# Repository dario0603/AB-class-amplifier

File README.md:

# Class-AB Audio Power Amplifier

## Overview

Design and simulation of a **Class-AB audio power amplifier**, focusing on output-stage linearity, crossover distortion reduction, and overcurrent protection.

The circuit combines an input amplification stage, diode-based biasing, and a complementary power output stage to achieve linear signal amplification. LTspice simulations are used to investigate the amplifier's transient response, frequency behavior, and current-limiting operation.

The project also explores the interaction between output-stage biasing, load current, and protection circuitry.

## Design Calculations

### 1. Power-Supply Smoothing Capacitor

The required smoothing capacitance is estimated using the empirical relationship for a full-wave rectifier:

$$
C \simeq \frac{I_{\mathrm{load}}}{2f \cdot \Delta V}
$$

where:
- $I_{\mathrm{load}}$ is the maximum load current.
- $f$ is the AC supply frequency.
- $\Delta V$ is the maximum allowable peak-to-peak ripple voltage.

Assuming a maximum load current of 3A, limited by the BJT-based output protection circuit, and a maximum ripple voltage of 2V, the required capacitance is approximately 15mF, assuming a 50Hz AC supply.

The implemented solution uses five 4700 $\mu$F capacitors connected in parallel, providing a nominal total capacitance of:

$$
C_{\mathrm{total}} = 5 \times 4700\mu\mathrm{F}
= 23.5\mathrm{mF}
$$

This capacitance exceeds the theoretical minimum and provides additional margin for smoothing the rectified voltage under load.

### 2. Output Current-Limit Protection

The positive and negative output-current limits are set by the current-sensing resistors $R_6$ and $R_7$. Using the approximate base-emitter voltage of a BJT, $V_{BE}\simeq 0.6\mathrm{V}$, the limiting currents can be estimated as:

$$
I_{\mathrm{max}+} \simeq \frac{0.6\mathrm{V}}{R_6}
$$

$$
I_{\mathrm{max}-} \simeq -\frac{0.6\mathrm{V}}{R_7}
$$

For a nominal current limit of approximately $\pm 3\mathrm{A}$, the required resistance values are:

$$
R_6 \simeq R_7 \simeq
\frac{0.6\mathrm{V}}{3\mathrm{A}}
= 0.2\Omega
$$

Using equal sensing resistances provides approximately symmetrical positive and negative current limits. The actual thresholds may differ due to transistor characteristics, temperature, and resistor tolerances.

### 3. Volume Control

Resistors $R_8$ and $R_9$ represent the upper and lower portions of a $10\mathrm{k}\Omega$ potentiometer used to adjust the amplifier's input level.

Rotating the potentiometer changes the voltage delivered to the following amplification stage, thereby controlling the audio volume.

### 4. Output power

Provided that overcurrent limiting is not triggered (i.e., the current remains below 3 A in magnitude), the maximum output voltage is given by \(V_{\mathrm{CC}} - 2V_{\gamma} - V_{\mathrm{ripple}}\). With a 32 V supply, this is approximately

$$
V_{\mathrm{out,max}} \simeq 32\mathrm{V} - 1.2\mathrm{V} - 2\mathrm{V} \simeq 28.8\mathrm{V}
$$

Considering the output voltage swing limitations of the TL082 operational amplifiers, whose maximum output voltage is approximately $V_{\mathrm{CC}} - 1.5\mathrm{V}$ and whose minimum output voltage is approximately \(1.5\mathrm{V}\), the maximum voltage swing is

$$
V_{\mathrm{pp}} \simeq 28.8\mathrm{V} - 1.5\mathrm{V} - 1.5\mathrm{V} \simeq 25.8\mathrm{V}
$$

Assuming a sinusoidal output signal, the maximum output power can be estimated as

$$
P_{\mathrm{out}} = \frac{V_{\mathrm{pp}}^2}{8R_{\mathrm{load}}}
$$

For a $4\Omega$ load, the maximum output power is approximately

$$
P_{\mathrm{out}} = \frac{25.8^2}{8 \cdot 4} \approx 20.8\,\mathrm{W}
$$

For an $8\Omega$ load, the maximum output power is approximately

$$
P_{\mathrm{out}} = \frac{25.8^2}{8 \cdot 8} \approx 10.4\mathrm{W}
$$

To increase the output power, the supply voltage $V\_{\mathrm{CC}}$ must be increased, while ensuring that the maximum supply voltage rating of the TL082 operational amplifiers is not exceeded.

## Simulation Results

### 1. Transient Response

The transient simulation compares the input signal $V_{in}$ with the output signal $V_{out}$.

The output waveform demonstrates the amplifier's ability to reproduce the input sinusoid with increased amplitude. The region around the zero crossing is particularly relevant for evaluating crossover distortion in the Class-AB output stage.

### 2. Frequency Response

The Bode plot shows the output-to-input transfer function in terms of gain magnitude and phase.

The simulated response exhibits a relatively flat passband up to approximately **100 kHz**, followed by high-frequency attenuation. The magnitude and phase responses provide insight into the amplifier's bandwidth and frequency-dependent behavior.

The voltage gain is set to the maximum value for this configuration, $A_v = 11 \simeq 20.8\text{dB}$.

### 3. Output Current Limiting

The current-limit simulation evaluates the behavior of the protection circuit under excessive output-current demand.

The circuit is designed to constrain the load current to approximately **±3 A**, helping protect the output transistors against overload conditions.

### 4. Current-Limit Transient Response

A closer view of the transient response highlights the behavior of the protection circuit during a current-limit event.

The simulation shows the current transient settling toward the intended limiting level. The observed settling time is approximately **12 ms** under the simulated conditions.

## PCB Design

The PCB layout was developed in KiCad based on the Class-AB audio power amplifier schematic. Particular attention was paid to component placement, power-stage routing, and current-carrying traces to ensure reliable operation.

The PCB design aims to minimize unwanted parasitic effects and provide suitable routing for the relatively high currents handled by the output stage. The placement of the output transistors and current-sensing resistors is particularly important for thermal management and current-limit protection.

### 1. PCB Layout

The following image shows the PCB layout designed in KiCad, including component placement and routing.

### 2. 3D PCB View

The 3D visualization provides a preview of the assembled PCB, showing the component placement and overall board layout. This view is useful for inspecting component positioning and evaluating the physical arrangement before manufacturing.

## Repository Structure

```text
.
├── README.md                               # Project documentation
├── img/                                    # Images and simulation results
├── KiCad/                                  # Schematics and PCB designs
│   └── mono_amplifier/
│       ├── AB_amp/                         # Class-AB amplifier design
│       ├── audio equalizer/                # Audio equalizer design
│       ├── mono_amplifier/                 # Main KiCad project — open this project only;
│       │                                   # the other designs are internally linked
│       └── power supply/                   # Power supply design
└── Spice/                                  # LTspice simulations
    └── opamp version/
        ├── AB amplifier final version.asc  # Final amplifier simulation
        ├── AB amplifier v1.asc             # Amplifier simulation, version 1
        ├── AB amplifier v2.asc             # Amplifier simulation, version 2
        └── AB amplifier v3.asc             # Amplifier simulation, version 3
```

> **Important:** Open only the main KiCad project file: `KiCad/mono_amplifier/mono_amplifier/mono_amplifier.kicad_pro`. The other KiCad designs are internally linked to this project.

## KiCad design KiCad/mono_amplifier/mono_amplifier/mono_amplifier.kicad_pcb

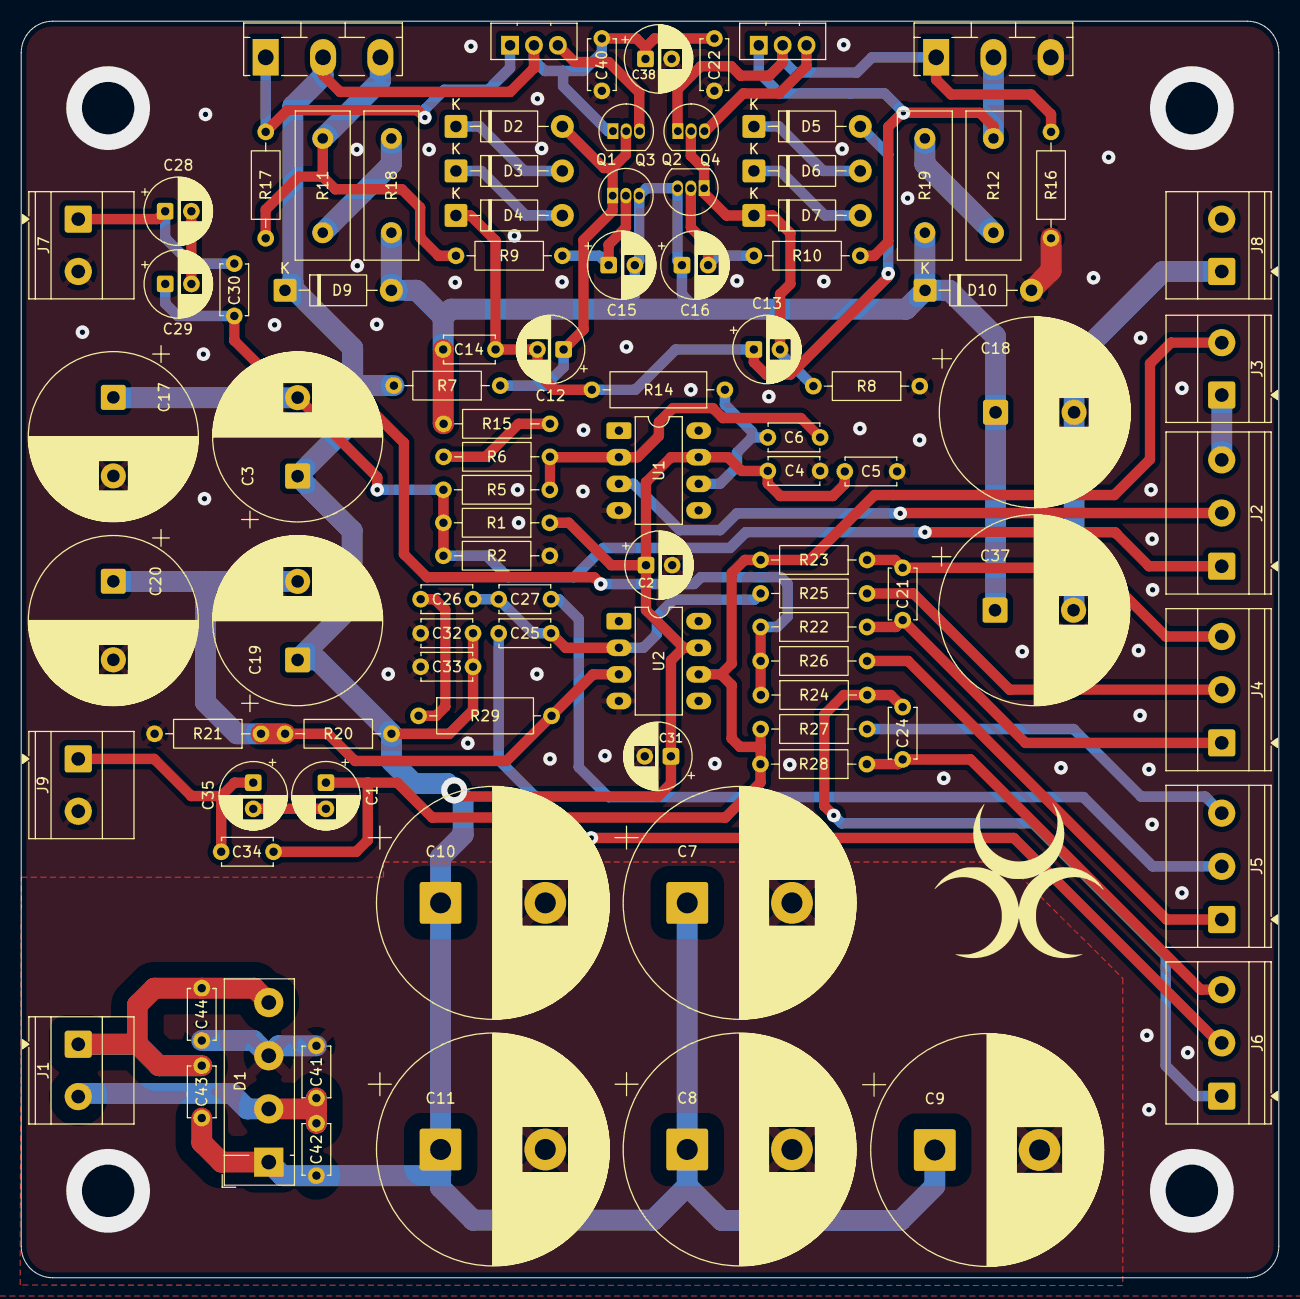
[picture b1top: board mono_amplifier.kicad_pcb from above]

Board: 2 copper layers, 120.1 x 120.0 mm, 95 parts (0 on the bottom side), 47 nets.

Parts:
C1, C2, C28, C29, C31, C35, C38: 100u; CP_Radial_D6.3mm_P2.50mm
C3, C17, C19, C20: 4700u; CP_Radial_D16.0mm_P7.50mm
C4, C30, C32, C34, C40: 10n; C_Disc_D4.7mm_W2.5mm_P5.00mm
C5, C14, C22, C33, C41, C42, C43, C44: 100p; C_Disc_D4.7mm_W2.5mm_P5.00mm
C6: 18p; C_Disc_D4.7mm_W2.5mm_P5.00mm
C7, C8, C9, C10, C11: 4700u; CP_Radial_D22.0mm_P10.00mm_SnapIn
C12, C13: 3u3; CP_Radial_D6.3mm_P2.50mm
C15, C16: 2u2; CP_Radial_D6.3mm_P2.50mm
C18, C37: 10000u; CP_Radial_D18.0mm_P7.50mm
C21: 47n; C_Disc_D4.7mm_W2.5mm_P5.00mm
C24, C27: 4n7; C_Disc_D4.7mm_W2.5mm_P5.00mm
C25: 22n; C_Disc_D4.7mm_W2.5mm_P5.00mm
C26: 1n; C_Disc_D4.7mm_W2.5mm_P5.00mm
D1: KBL04; Diode_Bridge_Vishay_KBL
D2, D3, D4, D5, D6, D7, D9, D10: 1N4148; D_DO-41_SOD81_P10.16mm_Horizontal
J1: Vin; TerminalBlock_Phoenix_MKDS-1,5-2_1x02_P5.00mm_Horizontal
J2: Pot_4k7; TerminalBlock_Phoenix_MKDS-1,5-3-5.08_1x03_P5.08mm_Horizont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
J3: Pot_switch; TerminalBlock_Phoenix_MKDS-1,5-2_1x02_P5.00mm_Horizontal
J4, J6: Pot_100k; TerminalBlock_Phoenix_MKDS-1,5-3-5.08_1x03_P5.08mm_Horizont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
J5: Pot_470k; TerminalBlock_Phoenix_MKDS-1,5-3-5.08_1x03_P5.08mm_Horizont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
J7: Input; TerminalBlock_Phoenix_MKDS-1,5-2_1x02_P5.00mm_Horizontal
J8: Output; TerminalBlock_Phoenix_MKDS-1,5-2_1x02_P5.00mm_Horizontal
J9: Output_preamp; TerminalBlock_Phoenix_MKDS-1,5-2_1x02_P5.00mm_Horizontal
Q1, Q3: BC337; TO-92_Inline
Q2, Q4: BC327; TO-92_Inline
Q5: BD139; TO-126-3_Vertical
Q6: BD140; TO-126-3_Vertical
Q7, Q8: TIP3055; TO-218-3_Vertical
R1, R2, R20, R21: 22k; R_Axial_DIN0207_L6.3mm_D2.5mm_P10.16mm_Horizontal
R5, R7, R8: 12k; R_Axial_DIN0207_L6.3mm_D2.5mm_P10.16mm_Horizontal
R6: 120k; R_Axial_DIN0207_L6.3mm_D2.5mm_P10.16mm_Horizontal
R9, R10: 100; R_Axial_DIN0207_L6.3mm_D2.5mm_P10.16mm_Horizontal
R11, R12, R18, R19: 0.1 5W; R_Box_L14.0mm_W5.0mm_P9.00mm
R14, R29: 270; R_Axial_DIN0309_L9.0mm_D3.2mm_P12.70mm_Horizontal
R15: 47k; R_Axial_DIN0207_L6.3mm_D2.5mm_P10.16mm_Horizontal
R16, R17: 1k; R_Axial_DIN0207_L6.3mm_D2.5mm_P10.16mm_Horizontal
R22, R23, R25: 10k; R_Axial_DIN0207_L6.3mm_D2.5mm_P10.16mm_Horizontal
R24, R28: 3k3; R_Axial_DIN0207_L6.3mm_D2.5mm_P10.16mm_Horizontal
R26, R27: 1k8; R_Axial_DIN0207_L6.3mm_D2.5mm_P10.16mm_Horizontal
U1, U2: TL081; DIP-8_W7.62mm_LongPads

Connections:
Audio_in: C28.1, C30.1, J7.1
GND: C2.2, C4.2, C5.2, C7.2, C8.2, C9.2, C10.2, C11.2, C17.2, C20.2, C22.2, C31.2, C32.2, C33.2, C38.2, C40.2, C41.2, C44.2, D1.3 (-), D10.2 (A), J7.2, J8.2, J9.2, Q8.3 (E), R2.2, R8.1, R16.1, R21.2, U1.4 (V-), U2.4 (V-)
unnamed: C1.2, C35.2
unnamed: C6.2, R14.1, U1.6
unnamed: C26.2, R29.1
unnamed: C28.2, C29.2
unnamed: C29.1, C30.2, R22.1, R24.1, R26.1
unnamed: C12.1, D2.2 (A), Q1.2 (B), Q3.1 (C), R7.1
unnamed: D2.1 (K), D3.2 (A)
unnamed: D3.1 (K), D4.2 (A)
unnamed: C12.2, C13.1, C14.1, D4.1 (K), D5.2 (A), R14.2
unnamed: D5.1 (K), D6.2 (A)
unnamed: D6.1 (K), D7.2 (A)
unnamed: C13.2, D7.1 (K), Q2.2 (B), Q4.1 (C), R8.2
unnamed: C14.2, C15.2, C16.1, C18.1, C37.1, D9.2 (A), D10.1 (K), Q3.3 (E), Q4.3 (E), R15.2, R18.2, R19.2
unnamed: C43.2, C44.1, D1.4, J1.1
unnamed: C41.1, C42.2, D1.2, J1.2
unnamed: C3.2, C17.1, J2.1, R1.2, R2.1, R5.1
unnamed: J2.2, U1.3 (+)
unnamed: J2.3, J3.1
unnamed: C21.1, J4.1, R22.2
unnamed: J4.2, R25.1
unnamed: C21.2, J4.3, R23.1
unnamed: J5.1, R26.2
unnamed: C27.1, J5.2
unnamed: J5.3, R27.1
unnamed: C24.1, J6.1, R24.2
unnamed: C25.1, J6.2
unnamed: C24.2, J6.3, R28.1
unnamed: C34.2, C35.1, J9.1
unnamed: Q1.3 (E), Q5.3 (B)
unnamed: Q2.1 (C), Q6.2 (C), Q8.1 (B), R16.2
unnamed: Q2.3 (E), Q6.3 (B)
unnamed: C15.1, Q3.2 (B), R9.1
unnamed: C16.2, Q4.2 (B), R10.1
unnamed: Q5.1 (E), Q7.1 (B), R17.2
unnamed: Q6.1 (E), Q8.2 (C), R10.2, R12.1
unnamed: Q7.3 (E), R9.2, R11.1, R17.1
unnamed: R11.2, R18.1
unnamed: R12.2, R19.1
unnamed: R6.2, R15.1
unnamed: C6.1, R5.2, R6.1, U1.2 (-)
unnamed: C19.2, C20.1, R20.2, R21.1, R29.2, U2.3 (+)
unnamed: C25.2, C26.1, C27.2, R25.2, U2.2 (-)
Preamp_out: C1.1, C34.1, J3.2, R23.2, R27.2, R28.2, U2.6
VCC: C2.1, C3.1, C4.1, C5.1, C7.1, C8.1, C9.1, C10.1, C11.1, C19.1, C22.1, C31.1, C32.1, C33.1, C38.1, C40.1, C42.1, C43.1, D1.1 (+), D9.1 (K), Q1.1 (C), Q5.2 (C), Q7.2 (C), R1.1, R7.2, R20.1, U1.7 (V+), U2.7 (V+)
Vout: C18.2, C37.2, J8.1

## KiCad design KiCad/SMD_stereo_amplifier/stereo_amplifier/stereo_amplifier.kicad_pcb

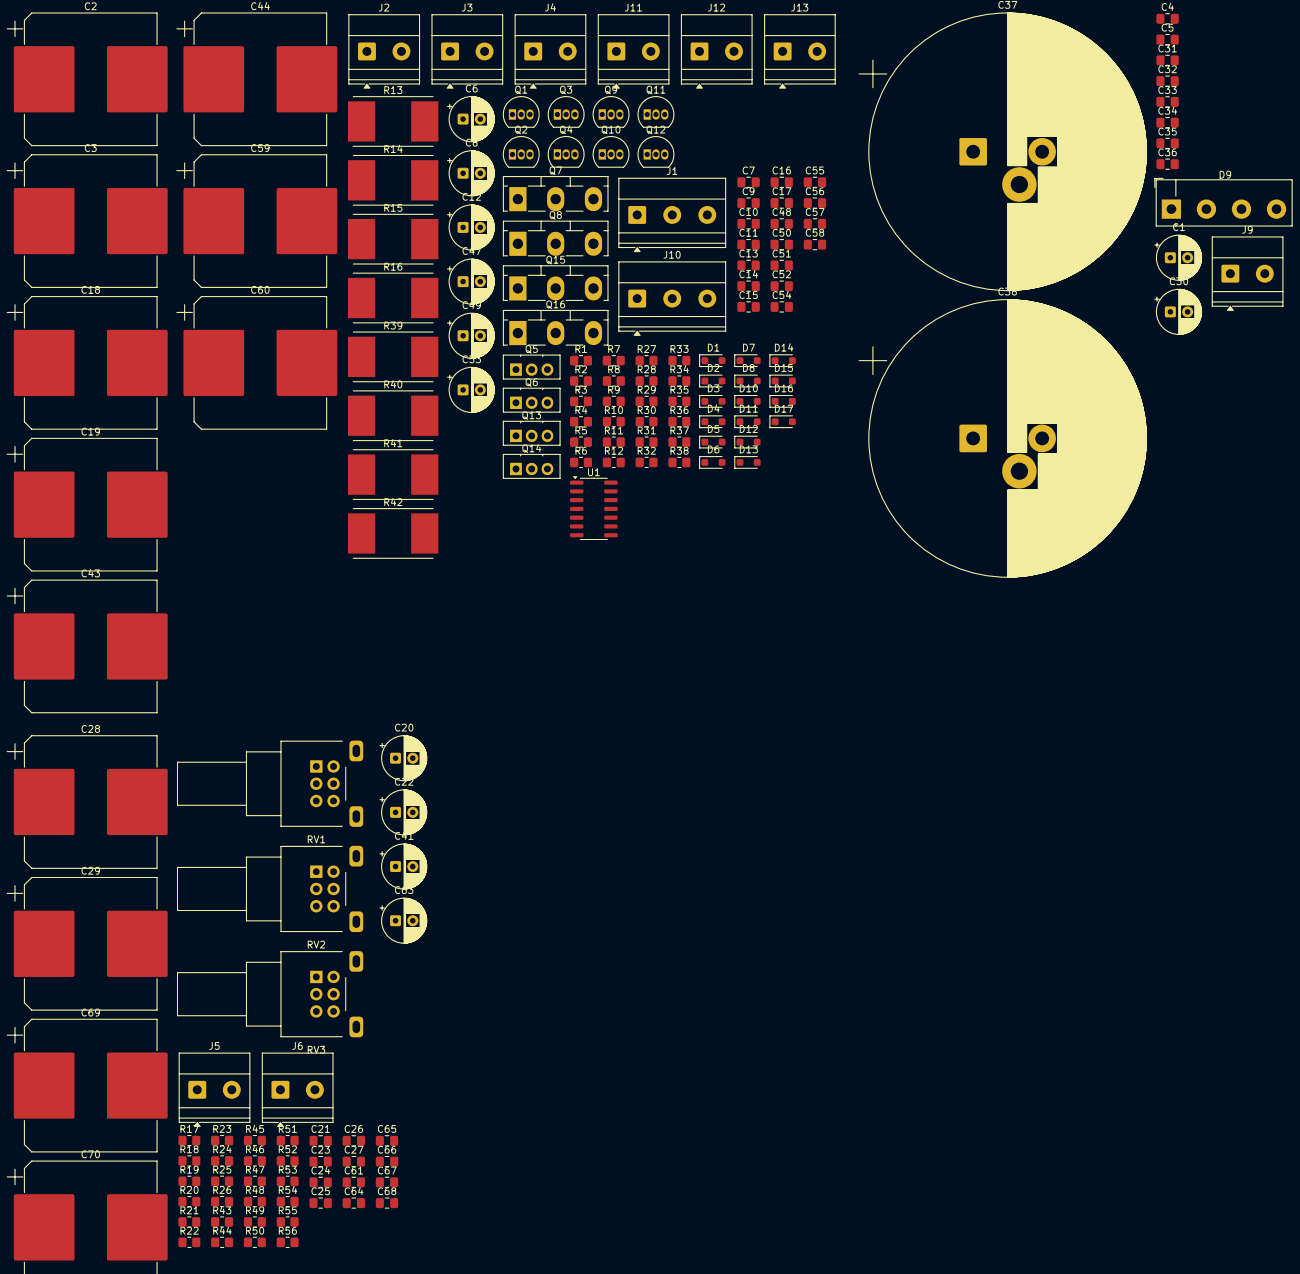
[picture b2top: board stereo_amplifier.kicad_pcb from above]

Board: 2 copper layers, 168 parts (0 on the bottom side), 93 nets, no tracks yet.

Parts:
C1, C6, C8, C12, C20, C22, C30, C41, C47, C49, C53, C63: 100u; CP_Radial_D6.3mm_P2.50mm
C2, C3, C18, C19, C28, C29, C43, C44, C59, C60, C69, C70: 1000u; CP_Elec_18x17.5
C4, C7, C11, C21, C31, C48, C52, C61: 10n; C_0805_2012Metric_Pad1.18x1.45mm_HandSolder
C5, C10, C15, C32, C33, C34, C35, C36, C51, C56: 100p; C_0805_2012Metric_Pad1.18x1.45mm_HandSolder
C9, C50: 18p; C_0805_2012Metric_Pad1.18x1.45mm_HandSolder
C13, C14, C54, C55: 3u3; C_0805_2012Metric_Pad1.18x1.45mm_HandSolder
C16, C17, C57, C58: 2u2; C_0805_2012Metric_Pad1.18x1.45mm_HandSolder
C23, C64: 47n; C_0805_2012Metric_Pad1.18x1.45mm_HandSolder
C24, C26, C65, C67: 4n7; C_0805_2012Metric_Pad1.18x1.45mm_HandSolder
C25, C66: 22n; C_0805_2012Metric_Pad1.18x1.45mm_HandSolder
C27, C68: 1n; C_0805_2012Metric_Pad1.18x1.45mm_HandSolder
C37, C38: 10000u; CP_Radial_D40.0mm_P10.00mm_3pin_SnapIn
D1, D2, D3, D4, D5, D6, D7, D8, D10, D11, D12, D13, D14, D15, D16, D17: 1N4148; D_SOD-323_HandSoldering
D9: KBL04; Diode_Bridge_Vishay_KBL
J1, J10: Pot_4k7; TerminalBlock_Phoenix_MKDS-1,5-3-5.08_1x03_P5.08mm_Horizont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
J2, J11: Pot_switch; TerminalBlock_Phoenix_MKDS-1,5-2_1x02_P5.00mm_Horizontal
J3: Output_preamp_R; TerminalBlock_Phoenix_MKDS-1,5-2_1x02_P5.00mm_Horizontal
J4: Output_R; TerminalBlock_Phoenix_MKDS-1,5-2_1x02_P5.00mm_Horizontal
J5, J6: Input; TerminalBlock_Phoenix_MKDS-1,5-2_1x02_P5.00mm_Horizontal
J9: Vin; TerminalBlock_Phoenix_MKDS-1,5-2_1x02_P5.00mm_Horizontal
J12: Output_preamp_L; TerminalBlock_Phoenix_MKDS-1,5-2_1x02_P5.00mm_Horizontal
J13: Output_L; TerminalBlock_Phoenix_MKDS-1,5-2_1x02_P5.00mm_Horizontal
Q1, Q3, Q9, Q11: BC337; TO-92_Inline
Q2, Q4, Q10, Q12: BC327; TO-92_Inline
Q5, Q13: BD139; TO-126-3_Vertical
Q6, Q14: BD140; TO-126-3_Vertical
Q7, Q8, Q15, Q16: TIP3055; TO-218-3_Vertical
R1, R2, R25, R26, R27, R28, R55, R56: 22k; R_0805_2012Metric_Pad1.20x1.40mm_HandSolder
R3, R29: 12k; R_0805_2012Metric_Pad1.20x1.40mm_HandSolder
R4, R30: 120k; R_0805_2012Metric_Pad1.20x1.40mm_HandSolder
R5, R31: 47k; R_0805_2012Metric_Pad1.20x1.40mm_HandSolder
R6, R24, R32, R54: 270; R_0805_2012Metric_Pad1.20x1.40mm_HandSolder
R7, R8, R33, R34: 220k; R_0805_2012Metric_Pad1.20x1.40mm_HandSolder
R9, R10, R35, R36: 1k; R_0805_2012Metric_Pad1.20x1.40mm_HandSolder
R11, R12, R37, R38: 100; R_0805_2012Metric_Pad1.20x1.40mm_HandSolder
R13, R14, R15, R16, R39, R40, R41, R42: 0.1 5W; R_Shunt_Vishay_WSR2_WSR3
R17, R20, R21, R45, R50, R51: 10k; R_0805_2012Metric_Pad1.20x1.40mm_HandSolder
R18, R22, R46, R52: 3k3; R_0805_2012Metric_Pad1.20x1.40mm_HandSolder
R19, R23, R47, R53: 1k8; R_0805_2012Metric_Pad1.20x1.40mm_HandSolder
R43, R44, R48, R49: 187k; R_0805_2012Metric_Pad1.20x1.40mm_HandSolder
RV1, RV2, RV3: 100k; Potentiometer_Alps_RK09L_Double_Horizontal
U1: TL084; SOIC-14_3.9x8.7mm_P1.27mm

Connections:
/Three band equalizer/POT11_A: C23.1, R17.2, RV1.3
/Three band equalizer/POT11_B: C23.2, R21.1, RV1.1
/Three band equalizer/POT11_H: R20.1, RV1.2
/Three band equalizer/POT12_A: C64.1, R45.2, RV1.4
/Three band equalizer/POT12_B: C64.2, R51.1, RV1.6
/Three band equalizer/POT12_H: R50.1, RV1.5
/Three band equalizer/POT21_A: C24.1, R18.2, RV2.3
/Three band equalizer/POT21_B: C24.2, R22.1, RV2.1
/Three band equalizer/POT21_H: C25.1, RV2.2
/Three band equalizer/POT22_A: C65.1, R46.2, RV2.4
/Three band equalizer/POT22_B: C65.2, R52.1, RV2.6
/Three band equalizer/POT22_H: C66.1, RV2.5
/Three band equalizer/POT31_A: R44.1, RV3.3
/Three band equalizer/POT31_B: R43.1, RV3.1
/Three band equalizer/POT31_H: C26.1, RV3.2
/Three band equalizer/POT32_A: R48.1, RV3.4
/Three band equalizer/POT32_B: R49.1, RV3.6
/Three band equalizer/POT32_H: C67.1, RV3.5
Audio_in_R: C20.1, C21.1, C41.1, C61.1, J5.1, J6.1
GND: C1.2, C3.2, C4.2, C5.2, C10.2, C11.2, C12.2, C29.2, C30.2, C31.2, C32.2, C34.2, C36.2, C37.2, C38.2, C44.2, C51.2, C52.2, C53.2, C70.2, D8.2 (A), D9.3 (-), D17.2 (A), J3.2, J4.2, J5.2, J6.2, J12.2, J13.2, Q8.3 (E), Q16.3 (E), R2.2, R8.1, R10.1, R26.2, R28.2, R34.1, R36.1, R56.2, RV1.MP (MountPin), RV2.MP (MountPin), RV3.MP (MountPin), U1.11 (V-)
unnamed: C6.2, C8.2
unnamed: C9.2, R6.1, U1.8
unnamed: C20.2, C22.2
unnamed: C21.2, C22.1, R17.1, R18.1, R19.1
unnamed: C27.2, R24.1
unnamed: C41.2, C63.2
unnamed: C47.2, C49.2
unnamed: C50.2, R32.1, U1.14
unnamed: C61.2, C63.1, R45.1, R46.1, R47.1
unnamed: C68.2, R54.1
unnamed: C13.1, D1.2 (A), Q1.1 (C), Q3.2 (B), R7.1
unnamed: D1.1 (K), D2.2 (A)
unnamed: D2.1 (K), D3.2 (A)
unnamed: C13.2, C14.1, C15.1, D3.1 (K), D4.2 (A), R6.2
unnamed: D4.1 (K), D5.2 (A)
unnamed: D5.1 (K), D6.2 (A)
unnamed: C14.2, D6.1 (K), Q2.1 (C), Q4.2 (B), R8.2
unnamed: C15.2, C16.2, C17.1, C18.1, C19.1, D7.2 (A), D8.1 (K), Q1.3 (E), Q2.3 (E), R5.2, R14.2, R15.2
unnamed: C54.1, D10.2 (A), Q9.1 (C), Q11.2 (B), R33.1
unnamed: D10.1 (K), D11.2 (A)
unnamed: D11.1 (K), D12.2 (A)
unnamed: C54.2, C55.1, C56.1, D12.1 (K), D13.2 (A), R32.2
unnamed: D13.1 (K), D14.2 (A)
unnamed: D14.1 (K), D15.2 (A)
unnamed: C55.2, D15.1 (K), Q10.1 (C), Q12.2 (B), R34.2
unnamed: C56.2, C57.2, C58.1, C59.1, C60.1, D16.2 (A), D17.1 (K), Q9.3 (E), Q10.3 (E), R31.2, R41.2, R42.2
unnamed: C2.2, C3.1, J1.1, R1.2, R2.1, R3.1
unnamed: J1.2, U1.10 (+)
unnamed: J1.3, J2.1
unnamed: C7.2, C8.1, J3.1
unnamed: C33.2, C34.1, D9.4, J9.1
unnamed: C35.2, C36.1, D9.2, J9.2
unnamed: C43.2, C44.1, J10.1, R27.2, R28.1, R29.1
unnamed: J10.2, U1.12 (+)
unnamed: J10.3, J11.1
unnamed: C48.2, C49.1, J12.1
unnamed: C16.1, Q1.2 (B), R11.1
unnamed: C17.2, Q2.2 (B), R12.1
unnamed: Q3.3 (E), Q5.3 (B)
unnamed: Q4.1 (C), Q6.2 (C), Q8.1 (B), R10.2
unnamed: Q4.3 (E), Q6.3 (B)
unnamed: Q5.1 (E), Q7.1 (B), R9.2
unnamed: Q6.1 (E), Q8.2 (C), R12.2, R16.1
unnamed: Q7.3 (E), R9.1, R11.2, R13.1
unnamed: C57.1, Q9.2 (B), R37.1
unnamed: C58.2, Q10.2 (B), R38.1
unnamed: Q11.3 (E), Q13.3 (B)
unnamed: Q12.1 (C), Q14.2 (C), Q16.1 (B), R36.2
unnamed: Q12.3 (E), Q14.3 (B)
unnamed: Q13.1 (E), Q15.1 (B), R35.2
unnamed: Q14.1 (E), Q16.2 (C), R38.2, R40.1
unnamed: Q15.3 (E), R35.1, R37.2, R39.1
unnamed: R4.2, R5.1
unnamed: R13.2, R14.1
unnamed: R15.1, R16.2
unnamed: R19.2, R44.2
unnamed: R23.1, R43.2
unnamed: R30.2, R31.1
unnamed: R39.2, R41.1
unnamed: R40.2, R42.1
unnamed: R47.2, R48.2
unnamed: R49.2, R53.1
unnamed: C28.2, C29.1, R24.2, R25.2, R26.1, U1.3 (+)
unnamed: C25.2, C26.2, C27.1, R20.2, U1.2 (-)
unnamed: C69.2, C70.1, R54.2, R55.2, R56.1, U1.5 (+)
unnamed: C66.2, C67.2, C68.1, R50.2, U1.6 (-)
unnamed: C9.1, R3.2, R4.1, U1.9 (-)
unnamed: C50.1, R29.2, R30.1, U1.13 (-)
Preamp_out_L: C47.1, C48.1, J11.2
Preamp_out_R: C6.1, C7.1, J2.2, R21.2, R22.2, R23.2, R51.2, R52.2, R53.2, U1.1, U1.7
VCC: C1.1, C2.1, C4.1, C5.1, C10.1, C11.1, C12.1, C28.1, C30.1, C31.1, C32.1, C33.1, C35.1, C37.1, C38.1, C43.1, C51.1, C52.1, C53.1, C69.1, D7.1 (K), D9.1 (+), D16.1 (K), Q3.1 (C), Q5.2 (C), Q7.2 (C), Q11.1 (C), Q13.2 (C), Q15.2 (C), R1.1, R7.2, R25.1, R27.1, R33.2, R55.1, U1.4 (V+)
Vout_L: C59.2, C60.2, J13.1
Vout_R: C18.2, C19.2, J4.1
